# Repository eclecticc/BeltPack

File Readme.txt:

Belt: https://www.amazon.com/gp/product/B011R8SN52
PC: https://www.intel.com/content/dam/support/us/en/documents/mini-pcs/nuc-kits/NUC8i7HVK_TechProdSpec.pdf
Battery: https://www.amazon.com/Makita-BL1830B-2-Lithium-Ion-3-0Ah-Battery/dp/B01M2VEHDL/ref=dp_ob_title_hi
Battery contacts: https://www.ebay.com/itm/263629602762?ViewItem=&item=263629602762
Cable: https://www.ebay.com/itm/Power-Plug-Connector-Cable-Cord-For-HP-Dell-Samsung-ASUS-EEE-PC-Laptop-Adapter/371858630342?ssPageName=STRK%3AMEBIDX%3AIT&var=640834242520&_trksid=p2057872.m2749.l2649

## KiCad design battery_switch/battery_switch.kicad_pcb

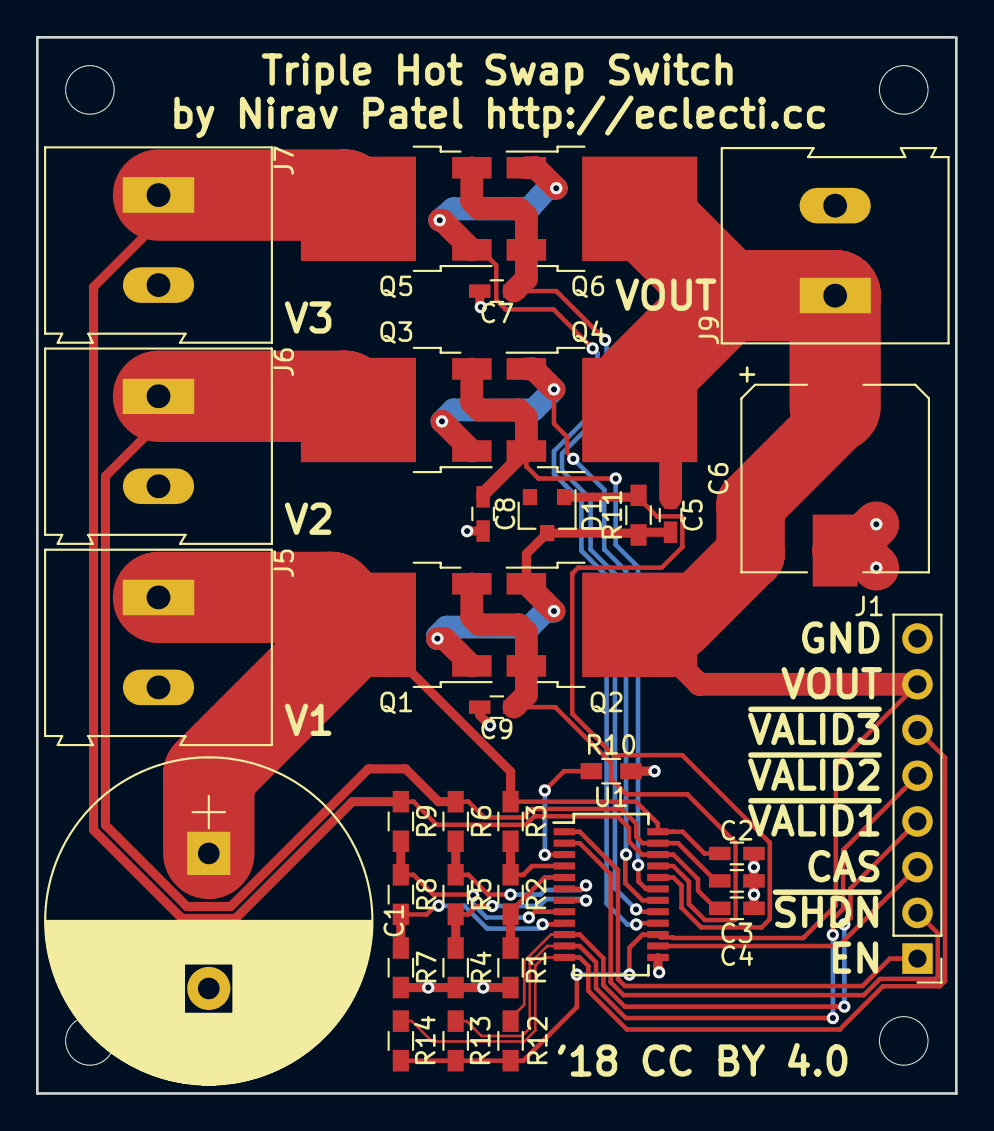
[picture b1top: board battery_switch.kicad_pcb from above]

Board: 2 copper layers, 51.1 x 58.7 mm, 36 parts (0 on the bottom side), 25 nets.

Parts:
C1: 2200uF; CP_Radial_D18.0mm_P7.50mm
C2, C3, C4, C7, C8, C9: 0.1uF; C_0603_HandSoldering
C5: 50nF; C_0603_HandSoldering
C6: 100uF; CP_Elec_10x10
D1: BAT54C; SOT-23
J1: Conn_01x08; PinHeader_1x08_P2.54mm_Vertical
J5, J6, J7, J9: Conn_01x02; TerminalBlock_Altech_AK300-2_P5.00mm
Q1, Q2, Q3, Q4, Q5, Q6: SUD50P04-08; TO-252-2
R1: 35.7k; R_0603_HandSoldering
R2: 24.3k; R_0603_HandSoldering
R3, R6, R9: 806k; R_0603_HandSoldering
R4, R7: 38.3k; R_0603_HandSoldering
R5, R8: 15.4k; R_0603_HandSoldering
R10: 252k; R_0603_HandSoldering
R11: 800; R_0603_HandSoldering
R12, R13, R14: 1M; R_0603_HandSoldering
U1: LTC4417CGN; SSOP-24_3.9x8.7mm_P0.635mm

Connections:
/CAS: J1.3, U1.14
/EN: J1.1, U1.1
/V1: C1.1, C2.1, J5.1, Q1.2, R3.1, U1.24
/V2: C3.1, J6.1, Q3.2, R6.1, U1.23
/V3: C4.1, J7.1, Q5.2, R9.1, U1.22
/VOUT: C5.1, C6.1, J1.7, J9.1, Q2.2, Q4.2, Q6.2, R12.1, R13.1, R14.1, U1.15
/~SHDN: J1.2, U1.2
/~VALID1: J1.4, R12.2, U1.10
/~VALID2: J1.5, R13.2, U1.11
/~VALID3: J1.6, R14.2, U1.12
GND: C1.2, C2.2, C3.2, C4.2, C6.2, C7.2, C8.2, C9.2, J1.8, J5.2, J6.2, J7.2, J9.2, R1.2, R4.2, R7.2, R10.2, U1.13
unnamed: C5.2, D1.3, Q1.1, Q2.1, R11.1
unnamed: C7.1, Q5.3, Q6.3, U1.17
unnamed: C8.1, Q3.3, Q4.3, U1.19
unnamed: C9.1, Q1.3, Q2.3, U1.21
unnamed: D1.1, R11.2, U1.20
unnamed: Q3.1, Q4.1, U1.18
unnamed: Q5.1, Q6.1, U1.16
unnamed: R1.1, R2.2, U1.5
unnamed: R2.1, R3.2, U1.4
unnamed: R4.1, R5.2, U1.7
unnamed: R5.1, R6.2, U1.6
unnamed: R7.1, R8.2, U1.9
unnamed: R8.1, R9.2, U1.8
unnamed: R10.1, U1.3

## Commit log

2018-06-03 initial repo
2018-06-24 Initial schematic for LTC4417 based switch
2018-06-25 Assign footprints and remove barrel connectors
2018-06-25 Partial layout
2018-06-26 completed layout
2025-05-27 Update pc link

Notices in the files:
battery_switch/battery_switch.kicad_pcb:
'18 CC BY 4.0
